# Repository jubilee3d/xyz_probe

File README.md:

# Jubilee XYZ Probe Tool
A touch probe for various measurement applications

## Overview
This is a Jubilee-compatible XYZ Probe.
It can act as a replacement for the existing z-limit switch or as a general means of inspecting items on the bed.
Probing gives the machine the ability to register against arbitrary features on the bed, enabling the possibility of resuming partial prints, scanning objects, or inspecting the existing dimensions of objects.

The XYZ probe can be reproduced from both printed and stock parts with a single unit costing about $50.
Simply order the parts in the [Shopping List](https://docs.google.com/spreadsheets/d/1exzQQtGWq62kmWazMUU2xbrfU62XK9QZYXhOB--K8R0/edit?usp=sharing) and follow the step-by-step instructions.

For more information on provisioning this tool for Jubilee, have a look at its corresponding [tool page](https://jubilee3d.com/index.php?title=XYZ_Probe_Tool).

## Specs
* probe the full XY volume. Probe *into* pockets up to 38 [mm] deep.
* compact! Does not sacrifice any of the build volume.
* Purchased Parts called out in the [Shopping List]()

## Community
This tool is part of the bigger ecosystem of Jubilee-compatible tools that implement the [E3D Toolchanger Coupler](https://github.com/e3donline/ToolChanger) standard.
For more on Jubilee, have a look at the [parent project](https://github.com/machineagency/jubilee) or join the [Discord](https://discord.gg/jubilee).

## Who made this?
This tool was created by [Joshua Vasquez](http://www.doublejumpelectric.com/) formerly at [Machine Agency](http://depts.washington.edu/machines/) at the University of Washington.

## Use the Source!
This tool is licensed with a [Creative Commons Attribution 4.0 Unported License](https://creativecommons.org/licenses/by/4.0/).

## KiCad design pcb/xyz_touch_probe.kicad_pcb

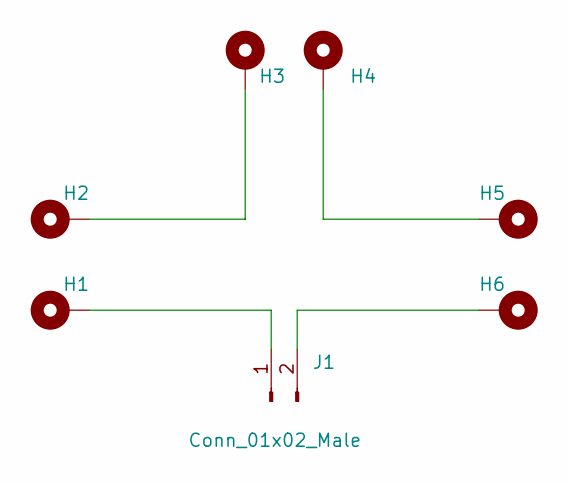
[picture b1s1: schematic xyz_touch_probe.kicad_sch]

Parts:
H1, H2, H3, H4, H5, H6: MountingHole_Pad; MountingHole_3.2mm_M3_DIN965_Pad
J1: Conn_01x02_Male; PinHeader_1x02_P2.54mm_Vertical

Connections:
unnamed: H1.1, J1.1
unnamed: H2.1, H3.1
unnamed: H4.1, H5.1
unnamed: H6.1, J1.2

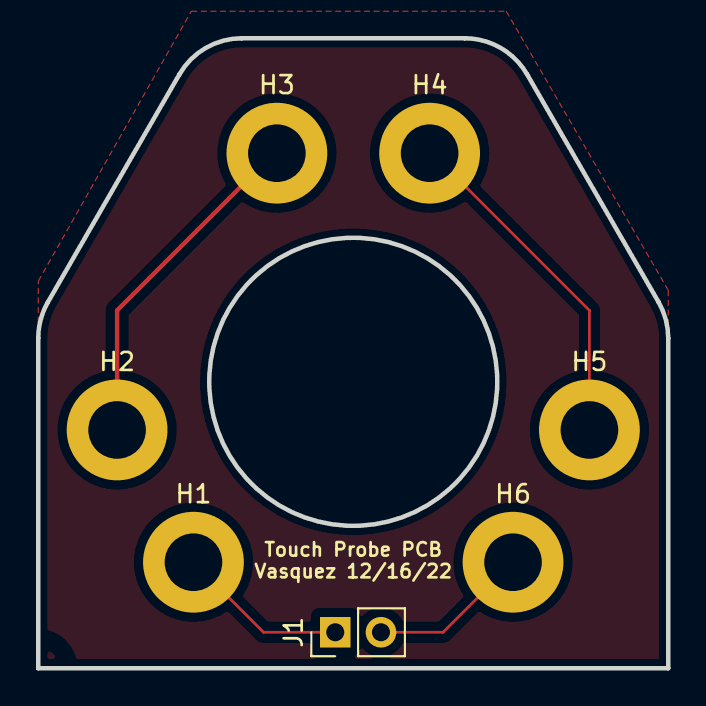
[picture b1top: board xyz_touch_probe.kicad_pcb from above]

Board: 2 copper layers, 35.0 x 35.0 mm, 7 parts (0 on the bottom side), 4 nets.

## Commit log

2022-12-28 add pcb
2022-12-28 add overview pdf
2022-12-28 add overview image
